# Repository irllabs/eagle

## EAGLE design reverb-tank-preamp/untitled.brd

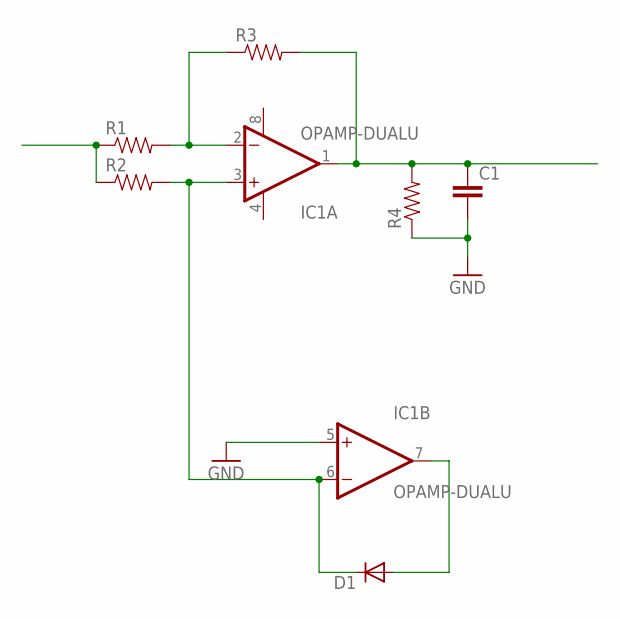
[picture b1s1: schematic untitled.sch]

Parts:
C1: CAP_; AXIAL-5MM
D1: DIODEPTH; DIODE-1N4001
IC1: OPAMP-DUALU; SO08
R1, R2, R3, R4: RESISTORPTH-1/6W; 1/6W-RES

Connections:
GND: C1.P$2 (2), IC1.5 (+IN), R4.1
unnamed: C1.P$1 (1), IC1.1 (OUT), R3.2, R4.2
unnamed: IC1.2 (-IN), R1.2, R3.1
unnamed: D1.C, IC1.3 (+IN), IC1.6 (-IN), R2.2
unnamed: D1.A, IC1.7 (OUT)
unnamed: R1.1, R2.1
V+: IC1.8 (V+)
V-: IC1.4 (V-)

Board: 2 copper layers, 7 parts (0 on the bottom side), 6 nets, no tracks yet.

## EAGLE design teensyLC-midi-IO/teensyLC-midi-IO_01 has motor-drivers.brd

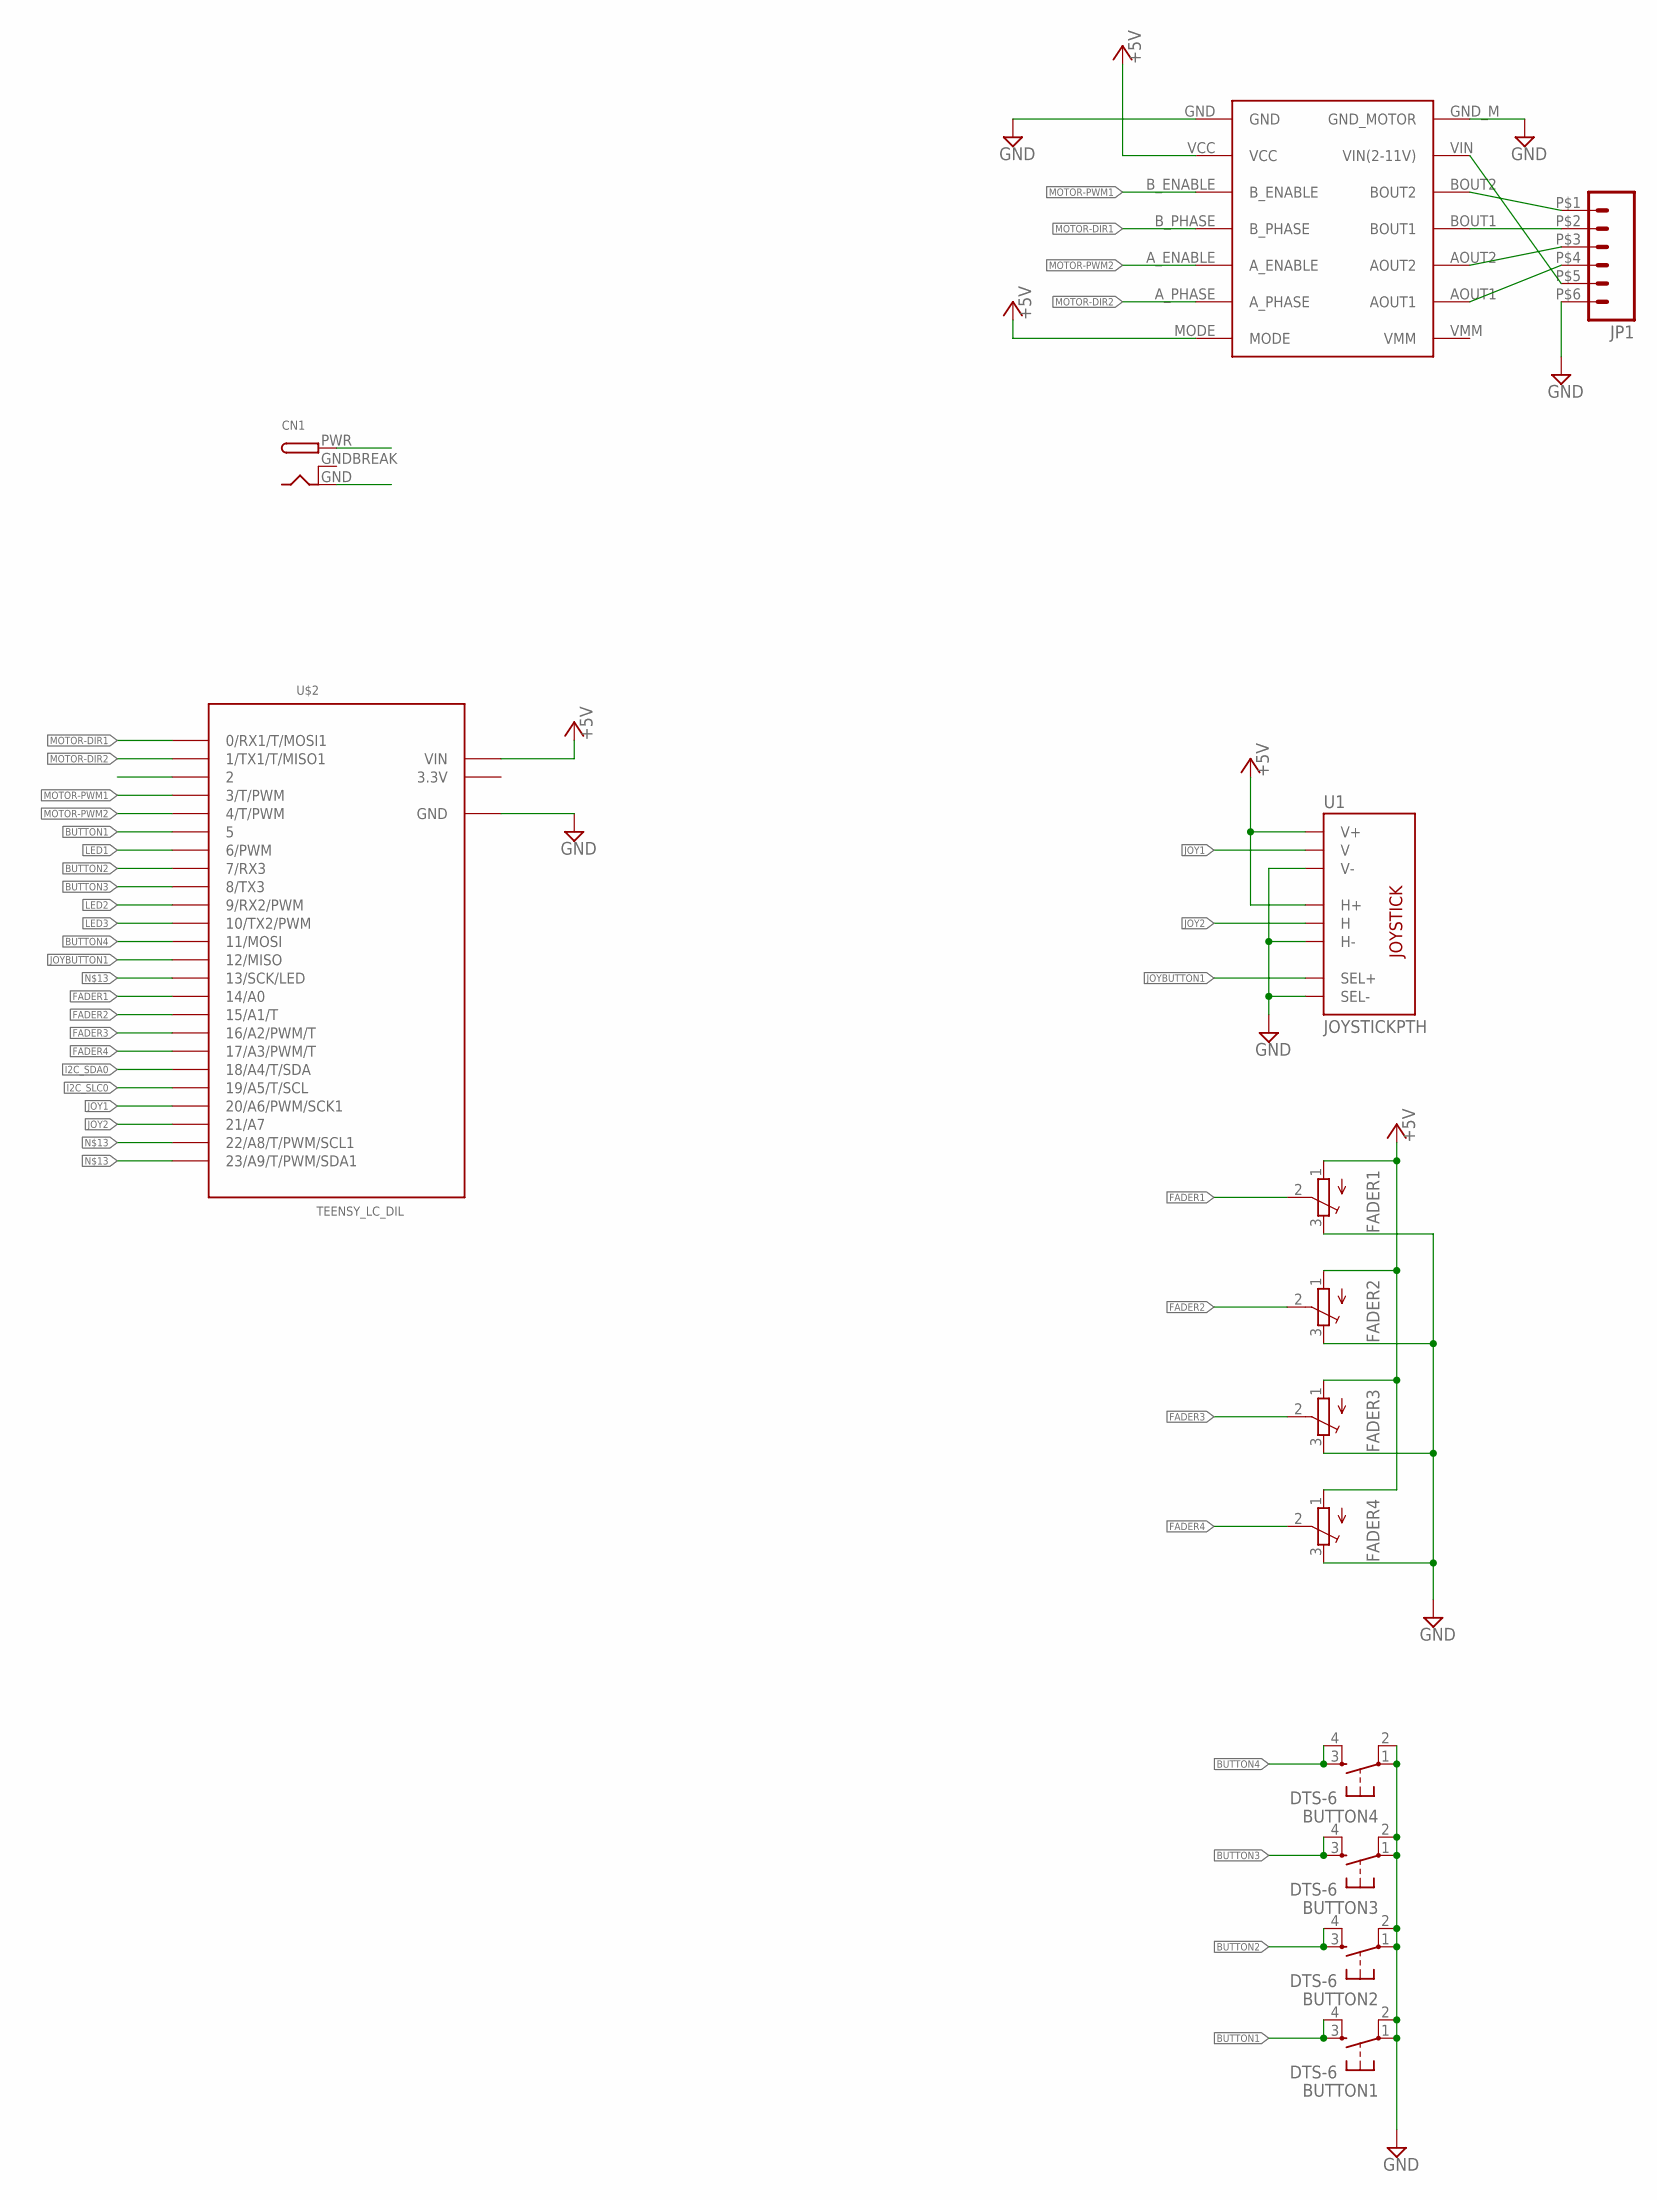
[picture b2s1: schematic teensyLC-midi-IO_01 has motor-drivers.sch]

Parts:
BUTTON1, BUTTON2, BUTTON3, BUTTON4: DTS-6
CN1: DCBARRELPTH; DCJACK_2MM_PTH
DRV1: POLOLU_DRV8835
FADER1, FADER2, FADER3, FADER4: TRIMPOT3386; TRIM-3386
JP1: M06; SPRINGTERMINAL-2.54MM-6
U1: JOYSTICKPTH; JOYSTICK
U$2: TEENSY_LC_DIL; TEENSY_3.0-3.2&LC_DIL

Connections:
3.3V: U$2.3.3V
12V: CN1.PWR, DRV1.VIN (VIN(2-11V)), JP1.P$5 (5)
+5V: DRV1.MODE, DRV1.VCC, FADER1.1 (A), FADER2.1 (A), FADER3.1 (A), FADER4.1 (A), U1.H1 (H+), U1.V1 (V+), U$2.VIN
ATTRU: JP1.P$6 (6)
BUTTON1: BUTTON1.3, BUTTON1.4, U$2.2, U$2.5
BUTTON2: BUTTON2.3, BUTTON2.4, U$2.7 (7/RX3)
BUTTON3: BUTTON3.3, BUTTON3.4, U$2.8 (8/TX3)
BUTTON4: BUTTON4.3, BUTTON4.4, U$2.11 (11/MOSI)
FADER1: FADER1.2 (S), U$2.14/A0
FADER2: FADER2.2 (S), U$2.15/A1 (15/A1/T)
FADER3: FADER3.2 (S), U$2.16/A2 (16/A2/PWM/T)
FADER4: FADER4.2 (S), U$2.17/A3 (17/A3/PWM/T)
GND: BUTTON1.1, BUTTON1.2, BUTTON2.1, BUTTON2.2, BUTTON3.1, BUTTON3.2, BUTTON4.1, BUTTON4.2, CN1.GND, DRV1.GND, DRV1.GND_M (GND_MOTOR), FADER1.3 (E), FADER2.3 (E), FADER3.3 (E), FADER4.3 (E), U1.B2A (SEL-), U1.H3 (H-), U1.V3 (V-), U$2.AGND (GND), U$2.GND
GNDBREAK: CN1.GNDBREAK
I2C_SDA0: U$2.18/A4 (18/A4/T/SDA)
I2C_SLC0: U$2.19/A5 (19/A5/T/SCL)
JOY1: U1.V2 (V), U$2.20/A6 (20/A6/PWM/SCK1)
JOY2: U1.H2 (H), U$2.21/A7
JOYBUTTON1: U1.B1A (SEL+), U$2.12 (12/MISO)
LED1: U$2.6 (6/PWM)
LED2: U$2.9 (9/RX2/PWM)
LED3: U$2.10 (10/TX2/PWM)
MOTOR-DIR1: DRV1.B_PHASE, U$2.0 (0/RX1/T/MOSI1)
MOTOR-DIR2: DRV1.A_PHASE, U$2.1 (1/TX1/T/MISO1)
MOTOR-PWM1: DRV1.B_ENABLE, U$2.3 (3/T/PWM)
MOTOR-PWM2: DRV1.A_ENABLE, U$2.4 (4/T/PWM)
unnamed: DRV1.AOUT1, JP1.P$4 (4)
unnamed: DRV1.AOUT2, JP1.P$3 (3)
unnamed: DRV1.BOUT1, JP1.P$2 (2)
unnamed: DRV1.BOUT2, JP1.P$1 (1)
unnamed: U$2.13 (13/SCK/LED), U$2.22/A8 (22/A8/T/PWM/SCL1), U$2.23/A9 (23/A9/T/PWM/SDA1)

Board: 2 copper layers, 13 parts (0 on the bottom side), 23 nets, no tracks yet.

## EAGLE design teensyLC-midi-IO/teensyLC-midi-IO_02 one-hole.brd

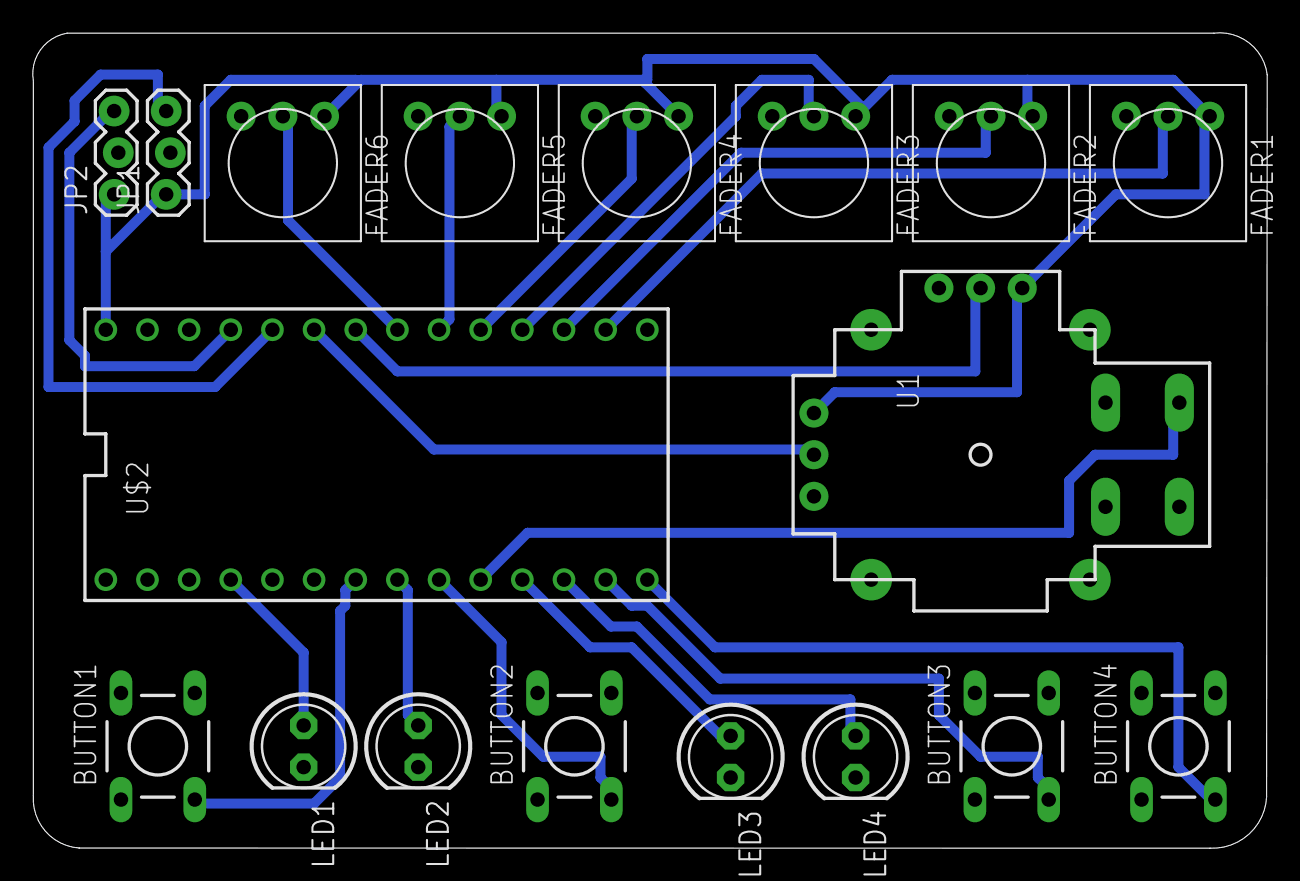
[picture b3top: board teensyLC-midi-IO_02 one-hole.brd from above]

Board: 2 copper layers, 75.3 x 49.7 mm, 18 parts (0 on the bottom side), 21 nets.

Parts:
BUTTON1, BUTTON2, BUTTON3, BUTTON4: DTS-6
FADER1, FADER2, FADER3, FADER4, FADER5, FADER6: TRIM-3386
JP1, JP2: 1X03_LOCK
LED1, LED2, LED3, LED4: LED5MM
U1: JOYSTICKPTH; JOYSTICK
U$2: TEENSY_LC_DIL; TEENSY_3.0-3.2&LC_DIL

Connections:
+5V: FADER1.1, FADER2.1, FADER3.1, FADER4.1, FADER5.1, FADER6.1, JP1.1, JP2.1, U1.H1, U1.V1, U$2.VIN
ANALOG1: JP1.3, U$2.22/A8
ANALOG2: JP2.3, U$2.23/A9
BUTTON1: BUTTON1.3, U$2.5
BUTTON2: BUTTON2.3, U$2.7
BUTTON3: BUTTON3.3, U$2.11
BUTTON4: BUTTON4.3, U$2.12
FADER1: FADER1.2, U$2.14/A0
FADER2: FADER2.2, U$2.15/A1
FADER3: FADER3.2, U$2.16/A2
FADER4: FADER4.2, U$2.17/A3
FADER5: FADER5.2, U$2.18/A4
FADER6: FADER6.2, U$2.19/A5
GND: BUTTON1.1, BUTTON2.1, BUTTON3.1, BUTTON4.1, FADER1.3, FADER2.3, FADER3.3, FADER4.3, FADER5.3, FADER6.3, JP1.2, JP2.2, LED1.K, LED2.K, LED3.K, LED4.K, U1.B2A, U1.H3, U1.V3, U$2.AGND, U$2.GND
JOY1: U1.V2, U$2.20/A6
JOY2: U1.H2, U$2.21/A7
JOYBUTTON1: U1.B1A, U$2.8
LED1: LED1.A, U$2.2
LED2: LED2.A, U$2.6
LED3: LED3.A, U$2.9
LED4: LED4.A, U$2.10

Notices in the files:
parts and their libraries:
SparkFun-AnalogIC: Licensing: CC v3.0 Share-Alike You are welcome to use this library for commercial purposes.
SparkFun-Connectors: Licensing: Creative Commons ShareAlike 4.0 International - https://creativecommons.org/licenses/by-sa/4.0
